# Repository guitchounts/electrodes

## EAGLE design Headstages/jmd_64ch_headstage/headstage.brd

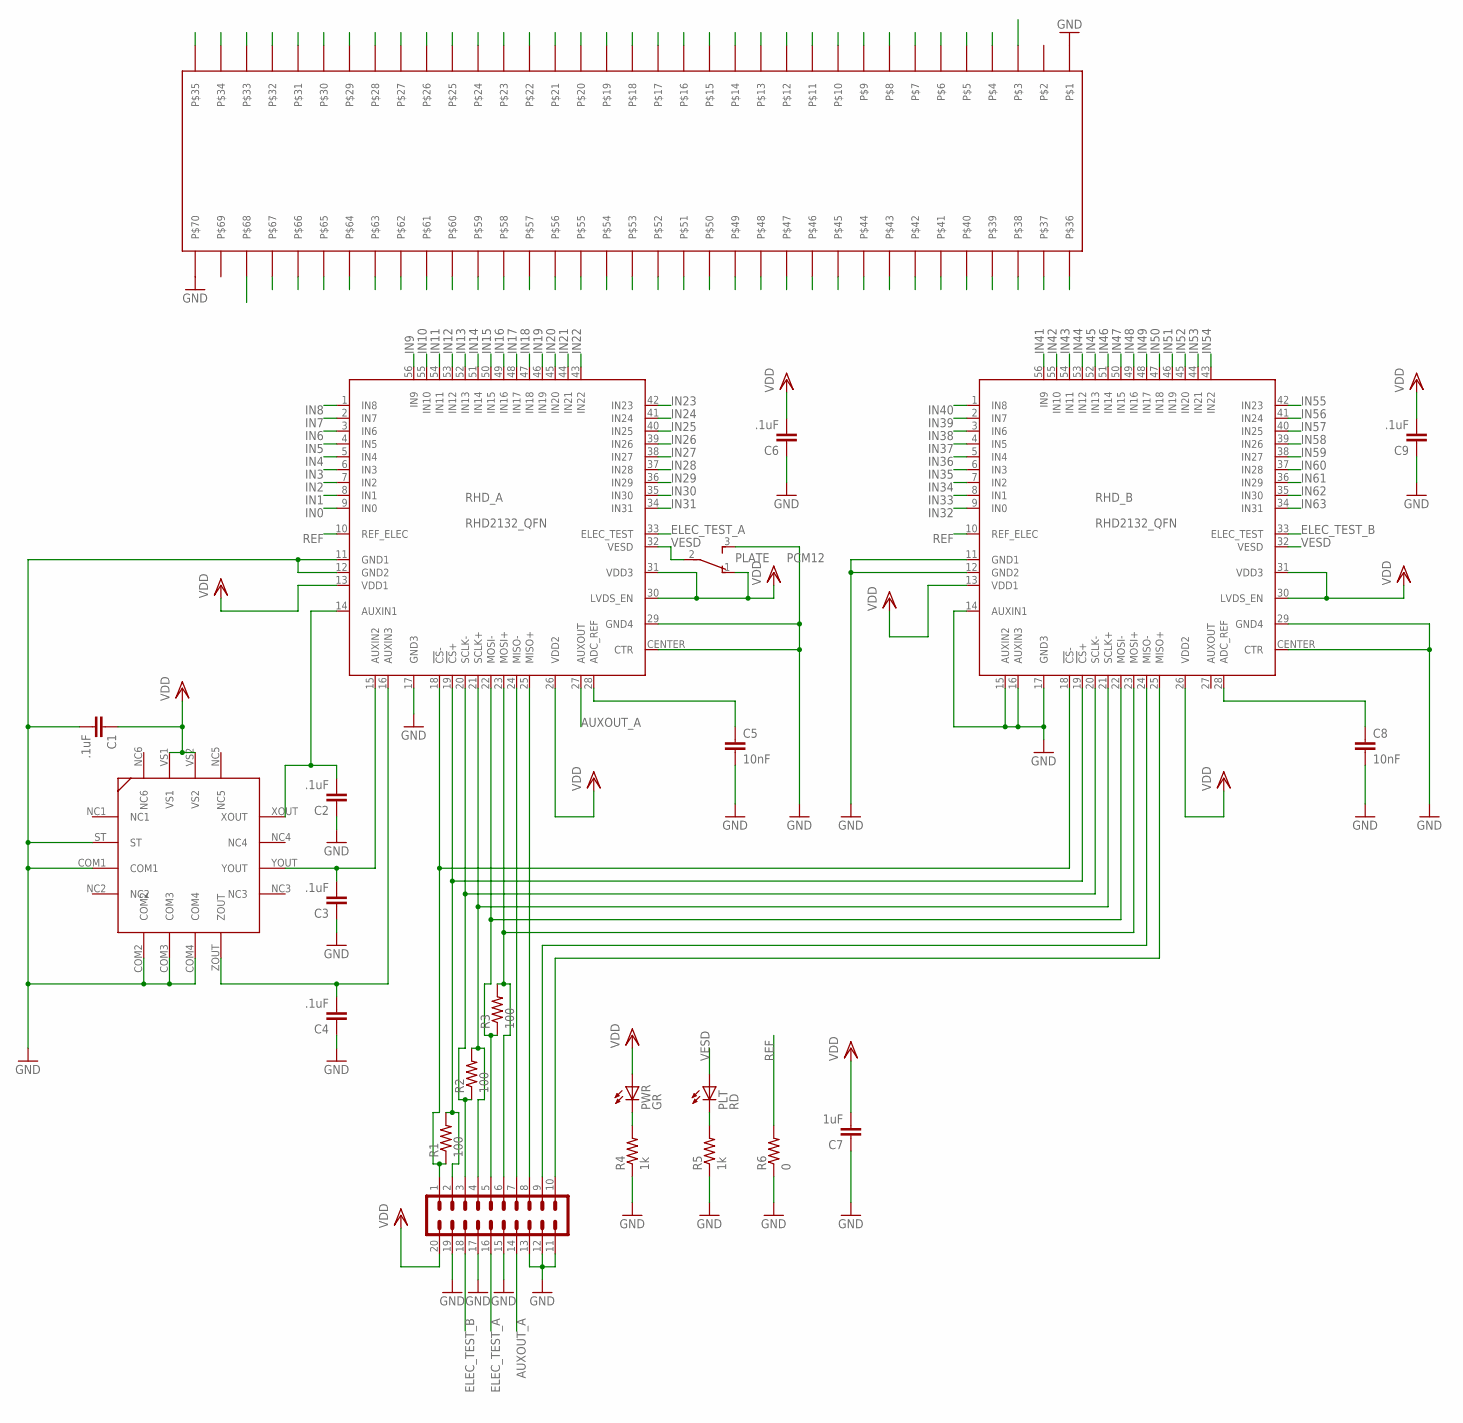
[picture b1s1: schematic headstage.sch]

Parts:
C1, C2, C3, C4: .1uF; 0402
C5, C8: 10nF; 0402
C6, C9: .1uF; 0603
C7: 1uF; 0603
OUT: JMD; JMD20-RA
PLATE: PCM12
PLT: RD; CHIP-LED0603
PWR: GR; CHIP-LED0603
R1, R2, R3: 100; 0402
R4, R5: 1k; 0402
R6: 0; 0402
RHD_A: RHD2132_QFN; QFN56_8_X_8_LARGE
RHD_B: RHD2132_QFN; QFN56_8_X_8_LARGE
U1: ADXL335
U$1: HIROSE_DF40_70PIN; HIROSE_DF40C-70DS

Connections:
AUXOUT_A: OUT.14, RHD_A.27 (AUXOUT)
CS+: OUT.2, R1.2, RHD_A.19 (!CS!+), RHD_B.19 (!CS!+)
CS-: OUT.1, R1.1, RHD_A.18 (!CS!-), RHD_B.18 (!CS!-)
ELEC_TEST_A: OUT.16, RHD_A.33 (ELEC_TEST)
ELEC_TEST_B: OUT.18, RHD_B.33 (ELEC_TEST)
GND: C1.2, C2.1, C3.1, C4.1, C5.2, C6.1, C7.1, C8.2, C9.1, OUT.11, OUT.12, OUT.13, OUT.15, OUT.17, OUT.19, PLATE.3, R4.1, R5.1, R6.1, RHD_A.11 (GND1), RHD_A.12 (GND2), RHD_A.17 (GND3), RHD_A.29 (GND4), RHD_A.CENTER (CTR), RHD_B.11 (GND1), RHD_B.12 (GND2), RHD_B.14 (AUXIN1), RHD_B.15 (AUXIN2), RHD_B.16 (AUXIN3), RHD_B.17 (GND3), RHD_B.29 (GND4), RHD_B.CENTER (CTR), U1.COM1, U1.COM2, U1.COM3, U1.COM4, U1.ST, U$1.P$1, U$1.P$70
IN0: RHD_A.9 (IN0), U$1.P$4
IN1: RHD_A.8 (IN1), U$1.P$5
IN2: RHD_A.7 (IN2), U$1.P$6
IN3: RHD_A.6 (IN3), U$1.P$7
IN4: RHD_A.5 (IN4), U$1.P$8
IN5: RHD_A.4 (IN5), U$1.P$9
IN6: RHD_A.3 (IN6), U$1.P$10
IN7: RHD_A.2 (IN7), U$1.P$11
IN8: RHD_A.1 (IN8), U$1.P$12
IN9: RHD_A.56 (IN9), U$1.P$13
IN10: RHD_A.55 (IN10), U$1.P$14
IN11: RHD_A.54 (IN11), U$1.P$15
IN12: RHD_A.53 (IN12), U$1.P$16
IN13: RHD_A.52 (IN13), U$1.P$17
IN14: RHD_A.51 (IN14), U$1.P$18
IN15: RHD_A.50 (IN15), U$1.P$19
IN16: RHD_A.49 (IN16), U$1.P$20
IN17: RHD_A.48 (IN17), U$1.P$21
IN18: RHD_A.47 (IN18), U$1.P$22
IN19: RHD_A.46 (IN19), U$1.P$23
IN20: RHD_A.45 (IN20), U$1.P$24
IN21: RHD_A.44 (IN21), U$1.P$25
IN22: RHD_A.43 (IN22), U$1.P$26
IN23: RHD_A.42 (IN23), U$1.P$27
IN24: RHD_A.41 (IN24), U$1.P$28
IN25: RHD_A.40 (IN25), U$1.P$29
IN26: RHD_A.39 (IN26), U$1.P$30
IN27: RHD_A.38 (IN27), U$1.P$31
IN28: RHD_A.37 (IN28), U$1.P$32
IN29: RHD_A.36 (IN29), U$1.P$33
IN30: RHD_A.35 (IN30), U$1.P$34
IN31: RHD_A.34 (IN31), U$1.P$35
IN32: RHD_B.9 (IN0), U$1.P$67
IN33: RHD_B.8 (IN1), U$1.P$66
IN34: RHD_B.7 (IN2), U$1.P$65
IN35: RHD_B.6 (IN3), U$1.P$64
IN36: RHD_B.5 (IN4), U$1.P$63
IN37: RHD_B.4 (IN5), U$1.P$62
IN38: RHD_B.3 (IN6), U$1.P$61
IN39: RHD_B.2 (IN7), U$1.P$60
IN40: RHD_B.1 (IN8), U$1.P$59
IN41: RHD_B.56 (IN9), U$1.P$58
IN42: RHD_B.55 (IN10), U$1.P$57
IN43: RHD_B.54 (IN11), U$1.P$56
IN44: RHD_B.53 (IN12), U$1.P$55
IN45: RHD_B.52 (IN13), U$1.P$54
IN46: RHD_B.51 (IN14), U$1.P$53
IN47: RHD_B.50 (IN15), U$1.P$52
IN48: RHD_B.49 (IN16), U$1.P$51
IN49: RHD_B.48 (IN17), U$1.P$50
IN50: RHD_B.47 (IN18), U$1.P$49
IN51: RHD_B.46 (IN19), U$1.P$48
IN52: RHD_B.45 (IN20), U$1.P$47
IN53: RHD_B.44 (IN21), U$1.P$46
IN54: RHD_B.43 (IN22), U$1.P$45
IN55: RHD_B.42 (IN23), U$1.P$44
IN56: RHD_B.41 (IN24), U$1.P$43
IN57: RHD_B.40 (IN25), U$1.P$42
IN58: RHD_B.39 (IN26), U$1.P$41
IN59: RHD_B.38 (IN27), U$1.P$40
IN60: RHD_B.37 (IN28), U$1.P$39
IN61: RHD_B.36 (IN29), U$1.P$38
IN62: RHD_B.35 (IN30), U$1.P$37
IN63: RHD_B.34 (IN31), U$1.P$36
LEDOUT1: PWR.C, R4.2
LEDOUT2: PLT.C, R5.2
MIS02-: OUT.9, RHD_B.24 (MISO-)
MISO1+: OUT.8, RHD_A.25 (MISO+)
MISO1-: OUT.7, RHD_A.24 (MISO-)
MISO2+: OUT.10, RHD_B.25 (MISO+)
MOSI+: OUT.6, R3.2, RHD_A.23 (MOSI+), RHD_B.23 (MOSI+)
MOSI-: OUT.5, R3.1, RHD_A.22 (MOSI-), RHD_B.22 (MOSI-)
unnamed: C8.1, RHD_B.28 (ADC_REF)
unnamed: C5.1, RHD_A.28 (ADC_REF)
REF: R6.2, RHD_A.10 (REF_ELEC), RHD_B.10 (REF_ELEC), U$1.P$3, U$1.P$68
SCLK+: OUT.4, R2.2, RHD_A.21 (SCLK+), RHD_B.21 (SCLK+)
SCLK-: OUT.3, R2.1, RHD_A.20 (SCLK-), RHD_B.20 (SCLK-)
VDD: C1.1, C6.2, C7.2, C9.2, OUT.20, PLATE.1, PWR.A, RHD_A.13 (VDD1), RHD_A.26 (VDD2), RHD_A.30 (LVDS_EN), RHD_A.31 (VDD3), RHD_B.13 (VDD1), RHD_B.26 (VDD2), RHD_B.30 (LVDS_EN), RHD_B.31 (VDD3), U1.VS1, U1.VS2
VESD: PLATE.2, PLT.A, RHD_A.32 (VESD), RHD_B.32 (VESD)
XOUT1: C2.2, RHD_A.14 (AUXIN1), U1.XOUT
YOUT1: C3.2, RHD_A.15 (AUXIN2), U1.YOUT
ZOUT1: C4.2, RHD_A.16 (AUXIN3), U1.ZOUT

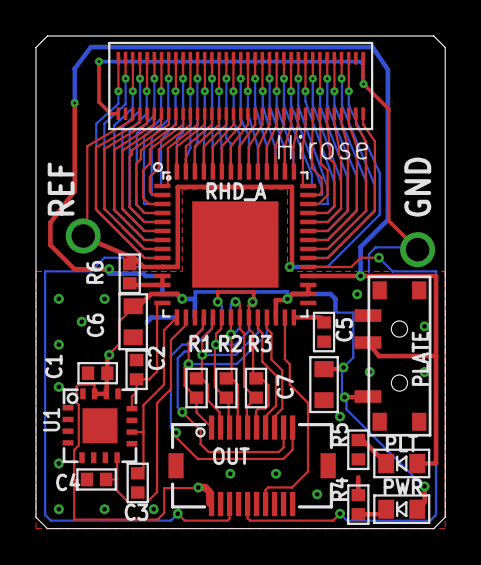
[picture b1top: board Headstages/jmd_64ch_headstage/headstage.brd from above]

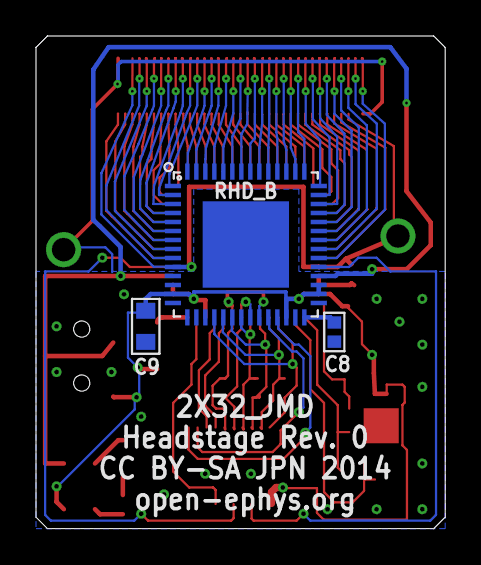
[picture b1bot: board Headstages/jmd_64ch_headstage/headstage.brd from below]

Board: 4 copper layers, 22.7 x 27.4 mm, 23 parts (3 on the bottom side), 88 nets.

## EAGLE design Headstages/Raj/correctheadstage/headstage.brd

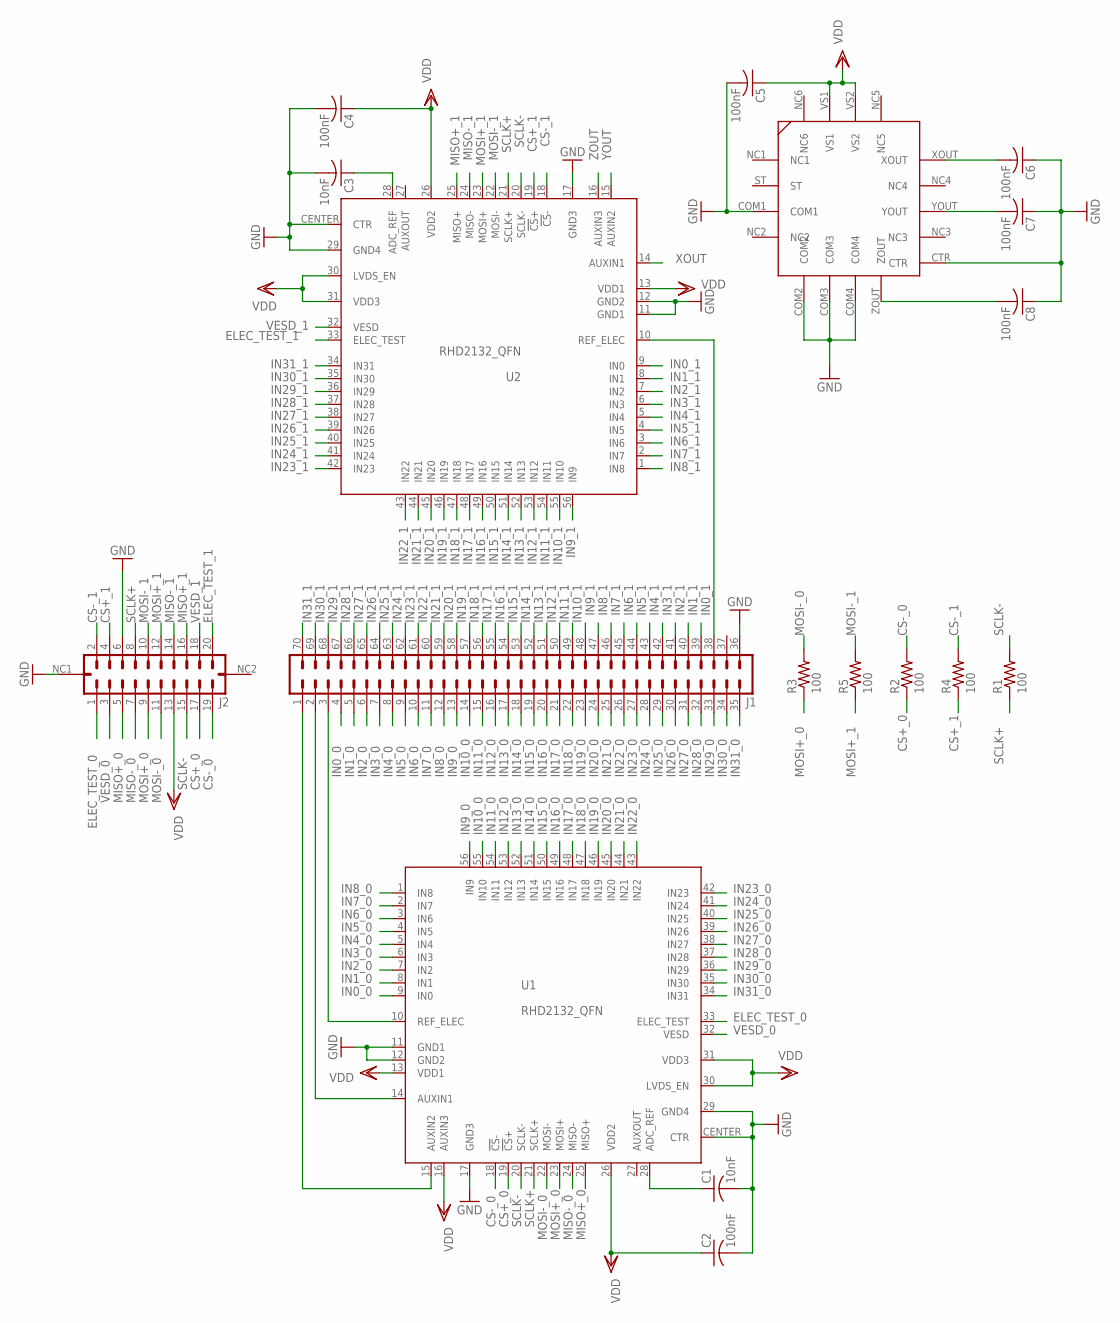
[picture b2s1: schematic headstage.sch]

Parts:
C1, C3: 10nF; C0402K
C2, C4, C5, C6, C7, C8: 100nF; C0402K
J1: HIROSE_DF40C-70DS-0.4V(51); HIROSE_DF40C-70DP
J2: MOLEX_501190-2017
R1, R2, R3, R4, R5: 100; R0402
U1, U2: RHD2132_QFN; QFN56_8_X_8_LARGE
U3: ADXL335

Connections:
CS+_0: J2.17, R2.1, U1.19 (!CS!+)
CS+_1: J2.4, R4.1, U2.19 (!CS!+)
CS-_0: J2.19, R2.2, U1.18 (!CS!-)
CS-_1: J2.2, R4.2, U2.18 (!CS!-)
ELEC_TEST_0: J2.1, U1.33 (ELEC_TEST)
ELEC_TEST_1: J2.20, U2.33 (ELEC_TEST)
GND: C1.2, C2.2, C3.2, C4.2, C5.2, C6.1, C7.1, C8.1, J1.36, J2.6, J2.NC1, U1.11 (GND1), U1.12 (GND2), U1.17 (GND3), U1.29 (GND4), U1.CENTER (CTR), U2.11 (GND1), U2.12 (GND2), U2.17 (GND3), U2.29 (GND4), U2.CENTER (CTR), U3.COM1, U3.COM2, U3.COM3, U3.COM4, U3.CTR
IN0_0: J1.4, U1.9 (IN0)
IN0_1: J1.39, U2.9 (IN0)
IN1_0: J1.5, U1.8 (IN1)
IN1_1: J1.40, U2.8 (IN1)
IN2_0: J1.6, U1.7 (IN2)
IN2_1: J1.41, U2.7 (IN2)
IN3_0: J1.7, U1.6 (IN3)
IN3_1: J1.42, U2.6 (IN3)
IN4_0: J1.8, U1.5 (IN4)
IN4_1: J1.43, U2.5 (IN4)
IN5_0: J1.9, U1.4 (IN5)
IN5_1: J1.44, U2.4 (IN5)
IN6_0: J1.10, U1.3 (IN6)
IN6_1: J1.45, U2.3 (IN6)
IN7_0: J1.11, U1.2 (IN7)
IN7_1: J1.46, U2.2 (IN7)
IN8_0: J1.12, U1.1 (IN8)
IN8_1: J1.47, U2.1 (IN8)
IN9_0: J1.13, U1.56 (IN9)
IN9_1: J1.48, U2.56 (IN9)
IN10_0: J1.14, U1.55 (IN10)
IN10_1: J1.49, U2.55 (IN10)
IN11_0: J1.15, U1.54 (IN11)
IN11_1: J1.50, U2.54 (IN11)
IN12_0: J1.16, U1.53 (IN12)
IN12_1: J1.51, U2.53 (IN12)
IN13_0: J1.17, U1.52 (IN13)
IN13_1: J1.52, U2.52 (IN13)
IN14_0: J1.18, U1.51 (IN14)
IN14_1: J1.53, U2.51 (IN14)
IN15_0: J1.19, U1.50 (IN15)
IN15_1: J1.54, U2.50 (IN15)
IN16_0: J1.20, U1.49 (IN16)
IN16_1: J1.55, U2.49 (IN16)
IN17_0: J1.21, U1.48 (IN17)
IN17_1: J1.56, U2.48 (IN17)
IN18_0: J1.22, U1.47 (IN18)
IN18_1: J1.57, U2.47 (IN18)
IN19_0: J1.23, U1.46 (IN19)
IN19_1: J1.58, U2.46 (IN19)
IN20_0: J1.24, U1.45 (IN20)
IN20_1: J1.59, U2.45 (IN20)
IN21_0: J1.25, U1.44 (IN21)
IN21_1: J1.60, U2.44 (IN21)
IN22_0: J1.26, U1.43 (IN22)
IN22_1: J1.61, U2.43 (IN22)
IN23_0: J1.27, U1.42 (IN23)
IN23_1: J1.62, U2.42 (IN23)
IN24_0: J1.28, U1.41 (IN24)
IN24_1: J1.63, U2.41 (IN24)
IN25_0: J1.29, U1.40 (IN25)
IN25_1: J1.64, U2.40 (IN25)
IN26_0: J1.30, U1.39 (IN26)
IN26_1: J1.65, U2.39 (IN26)
IN27_0: J1.31, U1.38 (IN27)
IN27_1: J1.66, U2.38 (IN27)
IN28_0: J1.32, U1.37 (IN28)
IN28_1: J1.67, U2.37 (IN28)
IN29_0: J1.33, U1.36 (IN29)
IN29_1: J1.68, U2.36 (IN29)
IN30_0: J1.34, U1.35 (IN30)
IN30_1: J1.69, U2.35 (IN30)
IN31_0: J1.35, U1.34 (IN31)
IN31_1: J1.70, U2.34 (IN31)
MISO+_0: J2.5, U1.25 (MISO+)
MISO+_1: J2.16, U2.25 (MISO+)
MISO-_0: J2.7, U1.24 (MISO-)
MISO-_1: J2.14, U2.24 (MISO-)
MOSI+_0: J2.9, R3.1, U1.23 (MOSI+)
MOSI+_1: J2.12, R5.1, U2.23 (MOSI+)
MOSI-_0: J2.11, R3.2, U1.22 (MOSI-)
MOSI-_1: J2.10, R5.2, U2.22 (MOSI-)
unnamed: J1.1, U1.15 (AUXIN2)
unnamed: J1.2, U1.14 (AUXIN1)
unnamed: C1.1, U1.28 (ADC_REF)
unnamed: C3.1, U2.28 (ADC_REF)
REF_ELEC_0: J1.3, U1.10 (REF_ELEC)
REF_ELEC_1: J1.38, U2.10 (REF_ELEC)
SCLK+: J2.8, R1.1, U1.21 (SCLK+), U2.21 (SCLK+)
SCLK-: J2.15, R1.2, U1.20 (SCLK-), U2.20 (SCLK-)
VDD: C2.1, C4.1, C5.1, J2.13, U1.13 (VDD1), U1.16 (AUXIN3), U1.26 (VDD2), U1.30 (LVDS_EN), U1.31 (VDD3), U2.13 (VDD1), U2.26 (VDD2), U2.30 (LVDS_EN), U2.31 (VDD3), U3.VS1, U3.VS2
VESD_0: J2.3, U1.32 (VESD)
VESD_1: J2.18, U2.32 (VESD)
XOUT: C6.2, U2.14 (AUXIN1), U3.XOUT
YOUT: C7.2, U2.15 (AUXIN2), U3.YOUT
ZOUT: C8.2, U2.16 (AUXIN3), U3.ZOUT

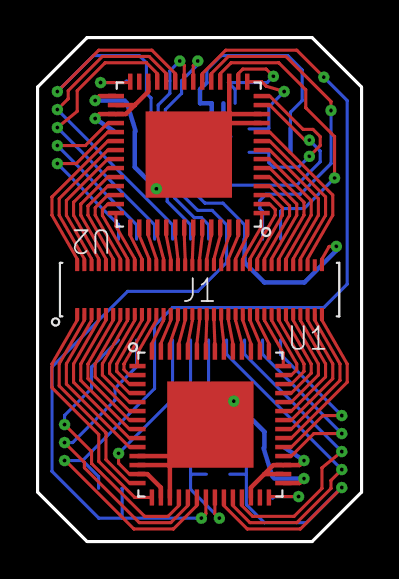
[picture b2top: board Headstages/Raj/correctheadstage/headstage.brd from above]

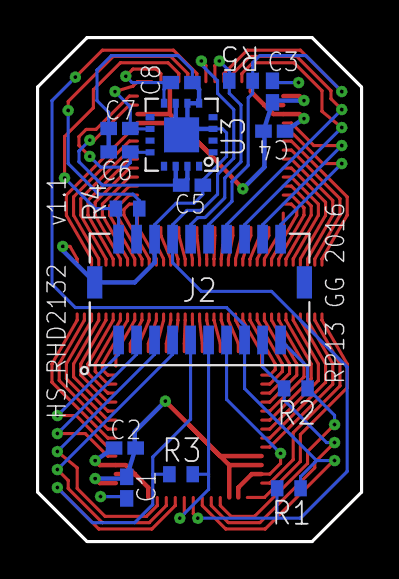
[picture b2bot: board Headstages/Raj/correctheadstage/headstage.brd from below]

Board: 4 copper layers, 18.0 x 28.0 mm, 18 parts (15 on the bottom side), 93 nets.

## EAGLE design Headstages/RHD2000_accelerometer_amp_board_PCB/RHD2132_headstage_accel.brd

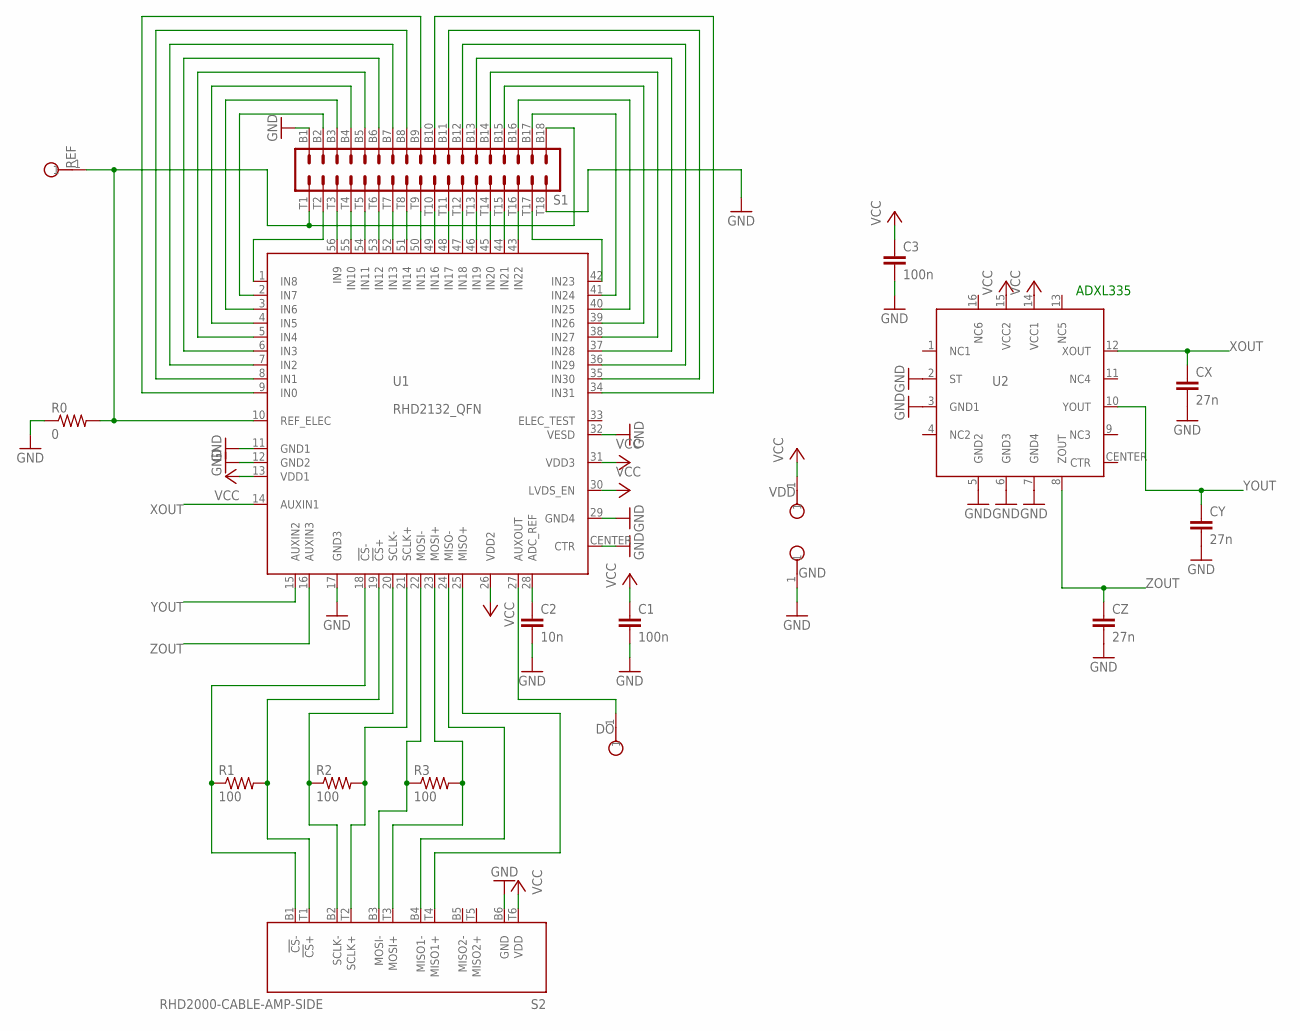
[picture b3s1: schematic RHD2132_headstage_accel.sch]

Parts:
C1, C3: 100n; 0402
C2: 10n; 0402
CX: 27n; 0402
CY: 27n; 0402
CZ: 27n; 0402
DO: TESTPOINT_SMALL
GND: TESTPOINT_SMALL
R0: 0; 0402
R1, R2, R3: 100; 0402
REF: TESTPOINT_SMALL
S1: OMNETICS_A79025
S2: RHD2000-CABLE-AMP-SIDE; OMNETICS_PZN-12-AA
U1: RHD2132_QFN; QFN56_8_X_8_LARGE
U2: ADXL335
VDD: TESTPOINT_SMALL

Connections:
GND: C1.2, C2.2, C3.2, CX.2, CY.2, CZ.2, GND.1, R0.1, S1.B1, S1.T18, S2.B6 (GND), U1.11 (GND1), U1.12 (GND2), U1.17 (GND3), U1.29 (GND4), U1.32 (VESD), U1.CENTER (CTR), U2.2 (ST), U2.3 (GND1), U2.5 (GND2), U2.6 (GND3), U2.7 (GND4)
unnamed: R0.2, REF.1, S1.B18, S1.T1, U1.10 (REF_ELEC)
unnamed: S1.B3, U1.3 (IN6)
unnamed: S1.B2, U1.2 (IN7)
unnamed: S1.B4, U1.4 (IN5)
unnamed: S1.B5, U1.5 (IN4)
unnamed: S1.B6, U1.6 (IN3)
unnamed: S1.B7, U1.7 (IN2)
unnamed: S1.B8, U1.8 (IN1)
unnamed: S1.B9, U1.9 (IN0)
unnamed: S1.B10, U1.34 (IN31)
unnamed: R1.1, S2.B1 (!CS!-), U1.18 (!CS!-)
unnamed: S1.B17, U1.41 (IN24)
unnamed: S1.B16, U1.40 (IN25)
unnamed: S1.B15, U1.39 (IN26)
unnamed: S1.B14, U1.38 (IN27)
unnamed: S1.B13, U1.37 (IN28)
unnamed: S1.B12, U1.36 (IN29)
unnamed: S1.B11, U1.35 (IN30)
unnamed: S1.T9, U1.50 (IN15)
unnamed: S1.T8, U1.51 (IN14)
unnamed: S1.T7, U1.52 (IN13)
unnamed: S1.T3, U1.56 (IN9)
unnamed: S1.T4, U1.55 (IN10)
unnamed: S1.T5, U1.54 (IN11)
unnamed: S1.T6, U1.53 (IN12)
unnamed: S1.T10, U1.49 (IN16)
unnamed: S1.T11, U1.48 (IN17)
unnamed: S1.T12, U1.47 (IN18)
unnamed: S1.T13, U1.46 (IN19)
unnamed: S1.T14, U1.45 (IN20)
unnamed: S1.T15, U1.44 (IN21)
unnamed: S1.T16, U1.43 (IN22)
unnamed: S1.T2, U1.1 (IN8)
unnamed: S1.T17, U1.42 (IN23)
unnamed: R1.2, S2.T1 (!CS!+), U1.19 (!CS!+)
unnamed: R2.1, S2.B2 (SCLK-), U1.20 (SCLK-)
unnamed: R2.2, S2.T2 (SCLK+), U1.21 (SCLK+)
unnamed: R3.1, S2.B3 (MOSI-), U1.22 (MOSI-)
unnamed: R3.2, S2.T3 (MOSI+), U1.23 (MOSI+)
unnamed: S2.B4 (MISO1-), U1.24 (MISO-)
unnamed: S2.T4 (MISO1+), U1.25 (MISO+)
unnamed: C2.1, U1.28 (ADC_REF)
unnamed: DO.1, U1.27 (AUXOUT)
VCC: C1.1, C3.1, S2.T6 (VDD), U1.13 (VDD1), U1.26 (VDD2), U1.30 (LVDS_EN), U1.31 (VDD3), U2.14 (VCC1), U2.15 (VCC2), VDD.1
XOUT: CX.1, U1.14 (AUXIN1), U2.12 (XOUT)
YOUT: CY.1, U1.15 (AUXIN2), U2.10 (YOUT)
ZOUT: CZ.1, U1.16 (AUXIN3), U2.8 (ZOUT)

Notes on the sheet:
ADXL335

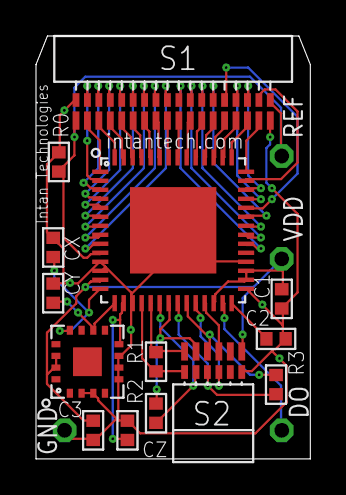
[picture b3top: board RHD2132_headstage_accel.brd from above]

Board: 4 copper layers, 15.2 x 23.5 mm, 18 parts (0 on the bottom side), 48 nets.

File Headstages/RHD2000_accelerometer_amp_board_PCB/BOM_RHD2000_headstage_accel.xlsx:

Bill of Materials |  | RHD2000 Headstage Accel Board |  | Intan Technologies, LLC
Part | Value | Device | Package | Digi-Key part number | Notes
C1 | 100 nF (0.1 uF) | ceramic capacitor (25 V) | 0402 | 445-4964-1-ND
C2 | 10 nF (10000 pF) | ceramic capacitor (25 V) | 0402 | 490-1312-1-ND
C3 | 100 nF (0.1 uF) | ceramic capacitor (25 V) | 0402 | 445-4964-1-ND
CX | 27 nF | ceramic capacitor (16 V) | 0402 | 399-4888-1-ND
CY | 27 nF | ceramic capacitor (16 V) | 0402 | 399-4888-1-ND
CZ | 27 nF | ceramic capacitor (16 V) | 0402 | 399-4888-1-ND
R0 | 0 | resistor | 0402 | P0.0JCT-ND
R1 | 100 | resistor | 0402 | P100JCT-ND
R2 | 100 | resistor | 0402 | P100JCT-ND
R3 | 100 | resistor | 0402 | P100JCT-ND
S1 | NSD-36-AA-GS | nano strip connector | 36-pin, 4 guides | Omnetics A79025-001
S2 | PZN-12-AA | polarized nano connector | polarized 12-pin | Omnetics A79623-001
U1 | RHD2132 or RHD2216 | 32-channel amplifier chip | QFN-56L | Intan RHD2132/RHD2216
U2 | ADXL335 | 3-axis accelerometer | LQFN-16 | ADXL335BCPZ-RL7CT-ND

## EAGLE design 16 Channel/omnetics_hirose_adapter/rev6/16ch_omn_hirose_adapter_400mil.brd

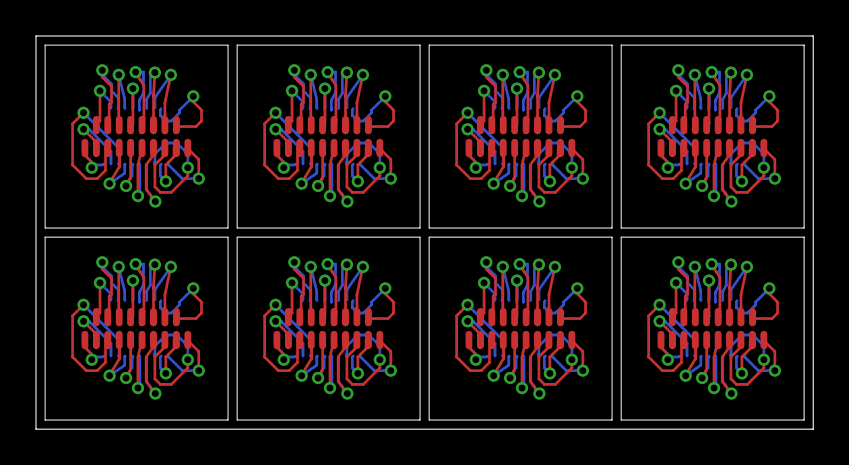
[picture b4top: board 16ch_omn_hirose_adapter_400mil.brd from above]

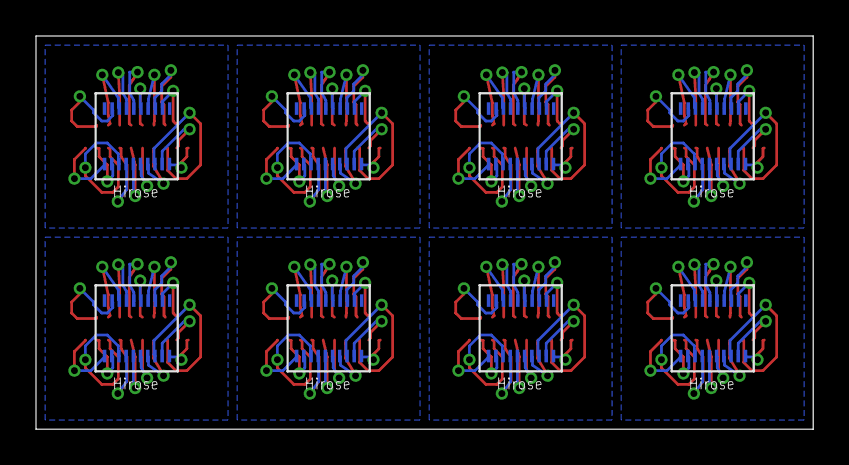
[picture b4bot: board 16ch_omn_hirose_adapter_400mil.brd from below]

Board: 2 copper layers, 43.2 x 21.8 mm, 16 parts (8 on the bottom side), 144 nets.

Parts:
U$1, U$3, U$5, U$7, U$9, U$11, U$13, U$15: HIROSE_DF40_70PIN; HIROSE_DF40C-70DS
U$2, U$4, U$6, U$8, U$10, U$12, U$14, U$16: OMNETICS_FE18

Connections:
unnamed: U$1.P$10, U$2.P$18
unnamed: U$1.P$9, U$2.P$8
unnamed: U$1.P$8, U$2.P$7
unnamed: U$1.P$7, U$2.P$6
unnamed: U$1.P$6, U$2.P$5
unnamed: U$1.P$5, U$2.P$4
unnamed: U$1.P$4, U$2.P$3
unnamed: U$1.P$3, U$2.P$2
unnamed: U$1.P$2, U$2.P$1
unnamed: U$1.P$1, U$2.P$17
unnamed: U$1.P$44, U$2.P$9
unnamed: U$1.P$43, U$2.P$10
unnamed: U$1.P$42, U$2.P$11
unnamed: U$1.P$41, U$2.P$12
unnamed: U$1.P$40, U$2.P$13
unnamed: U$1.P$39, U$2.P$14
unnamed: U$1.P$38, U$2.P$15
unnamed: U$1.P$37, U$2.P$16
unnamed: U$3.P$10, U$4.P$18
unnamed: U$3.P$9, U$4.P$8
unnamed: U$3.P$8, U$4.P$7
unnamed: U$3.P$7, U$4.P$6
unnamed: U$3.P$6, U$4.P$5
unnamed: U$3.P$5, U$4.P$4
unnamed: U$3.P$4, U$4.P$3
unnamed: U$3.P$3, U$4.P$2
unnamed: U$3.P$2, U$4.P$1
unnamed: U$3.P$1, U$4.P$17
unnamed: U$3.P$44, U$4.P$9
unnamed: U$3.P$43, U$4.P$10
unnamed: U$3.P$42, U$4.P$11
unnamed: U$3.P$41, U$4.P$12
unnamed: U$3.P$40, U$4.P$13
unnamed: U$3.P$39, U$4.P$14
unnamed: U$3.P$38, U$4.P$15
unnamed: U$3.P$37, U$4.P$16
unnamed: U$5.P$10, U$6.P$18
unnamed: U$5.P$9, U$6.P$8
unnamed: U$5.P$8, U$6.P$7
unnamed: U$5.P$7, U$6.P$6
unnamed: U$5.P$6, U$6.P$5
unnamed: U$5.P$5, U$6.P$4
unnamed: U$5.P$4, U$6.P$3
unnamed: U$5.P$3, U$6.P$2
unnamed: U$5.P$2, U$6.P$1
unnamed: U$5.P$1, U$6.P$17
unnamed: U$5.P$44, U$6.P$9
unnamed: U$5.P$43, U$6.P$10
unnamed: U$5.P$42, U$6.P$11
unnamed: U$5.P$41, U$6.P$12
unnamed: U$5.P$40, U$6.P$13
unnamed: U$5.P$39, U$6.P$14
unnamed: U$5.P$38, U$6.P$15
unnamed: U$5.P$37, U$6.P$16
unnamed: U$7.P$10, U$8.P$18
unnamed: U$7.P$9, U$8.P$8
unnamed: U$7.P$8, U$8.P$7
unnamed: U$7.P$7, U$8.P$6
unnamed: U$7.P$6, U$8.P$5
unnamed: U$7.P$5, U$8.P$4
unnamed: U$7.P$4, U$8.P$3
unnamed: U$7.P$3, U$8.P$2
unnamed: U$7.P$2, U$8.P$1
unnamed: U$7.P$1, U$8.P$17
unnamed: U$7.P$44, U$8.P$9
unnamed: U$7.P$43, U$8.P$10
unnamed: U$7.P$42, U$8.P$11
unnamed: U$7.P$41, U$8.P$12
unnamed: U$7.P$40, U$8.P$13
unnamed: U$7.P$39, U$8.P$14
unnamed: U$7.P$38, U$8.P$15
unnamed: U$7.P$37, U$8.P$16
unnamed: U$9.P$10, U$10.P$18
unnamed: U$9.P$9, U$10.P$8
unnamed: U$9.P$8, U$10.P$7
unnamed: U$9.P$7, U$10.P$6
unnamed: U$9.P$6, U$10.P$5
unnamed: U$9.P$5, U$10.P$4
unnamed: U$9.P$4, U$10.P$3
unnamed: U$9.P$3, U$10.P$2
unnamed: U$9.P$2, U$10.P$1
unnamed: U$9.P$1, U$10.P$17
unnamed: U$9.P$44, U$10.P$9
unnamed: U$9.P$43, U$10.P$10
unnamed: U$9.P$42, U$10.P$11
unnamed: U$9.P$41, U$10.P$12
unnamed: U$9.P$40, U$10.P$13
unnamed: U$9.P$39, U$10.P$14
unnamed: U$9.P$38, U$10.P$15
unnamed: U$9.P$37, U$10.P$16
unnamed: U$11.P$10, U$12.P$18
unnamed: U$11.P$9, U$12.P$8
unnamed: U$11.P$8, U$12.P$7
unnamed: U$11.P$7, U$12.P$6
unnamed: U$11.P$6, U$12.P$5
unnamed: U$11.P$5, U$12.P$4
unnamed: U$11.P$4, U$12.P$3
unnamed: U$11.P$3, U$12.P$2
unnamed: U$11.P$2, U$12.P$1
unnamed: U$11.P$1, U$12.P$17
unnamed: U$11.P$44, U$12.P$9
unnamed: U$11.P$43, U$12.P$10
unnamed: U$11.P$42, U$12.P$11
unnamed: U$11.P$41, U$12.P$12
unnamed: U$11.P$40, U$12.P$13
unnamed: U$11.P$39, U$12.P$14
unnamed: U$11.P$38, U$12.P$15
unnamed: U$11.P$37, U$12.P$16
unnamed: U$13.P$10, U$14.P$18
unnamed: U$13.P$9, U$14.P$8
unnamed: U$13.P$8, U$14.P$7
unnamed: U$13.P$7, U$14.P$6
unnamed: U$13.P$6, U$14.P$5
unnamed: U$13.P$5, U$14.P$4
unnamed: U$13.P$4, U$14.P$3
unnamed: U$13.P$3, U$14.P$2
unnamed: U$13.P$2, U$14.P$1
unnamed: U$13.P$1, U$14.P$17
unnamed: U$13.P$44, U$14.P$9
unnamed: U$13.P$43, U$14.P$10
unnamed: U$13.P$42, U$14.P$11
unnamed: U$13.P$41, U$14.P$12
unnamed: U$13.P$40, U$14.P$13
unnamed: U$13.P$39, U$14.P$14
unnamed: U$13.P$38, U$14.P$15
unnamed: U$13.P$37, U$14.P$16
unnamed: U$15.P$10, U$16.P$18
unnamed: U$15.P$9, U$16.P$8
unnamed: U$15.P$8, U$16.P$7
unnamed: U$15.P$7, U$16.P$6
unnamed: U$15.P$6, U$16.P$5
unnamed: U$15.P$5, U$16.P$4
unnamed: U$15.P$4, U$16.P$3
unnamed: U$15.P$3, U$16.P$2
unnamed: U$15.P$2, U$16.P$1
unnamed: U$15.P$1, U$16.P$17
unnamed: U$15.P$44, U$16.P$9
unnamed: U$15.P$43, U$16.P$10
unnamed: U$15.P$42, U$16.P$11
unnamed: U$15.P$41, U$16.P$12
unnamed: U$15.P$40, U$16.P$13
unnamed: U$15.P$39, U$16.P$14
unnamed: U$15.P$38, U$16.P$15
unnamed: U$15.P$37, U$16.P$16

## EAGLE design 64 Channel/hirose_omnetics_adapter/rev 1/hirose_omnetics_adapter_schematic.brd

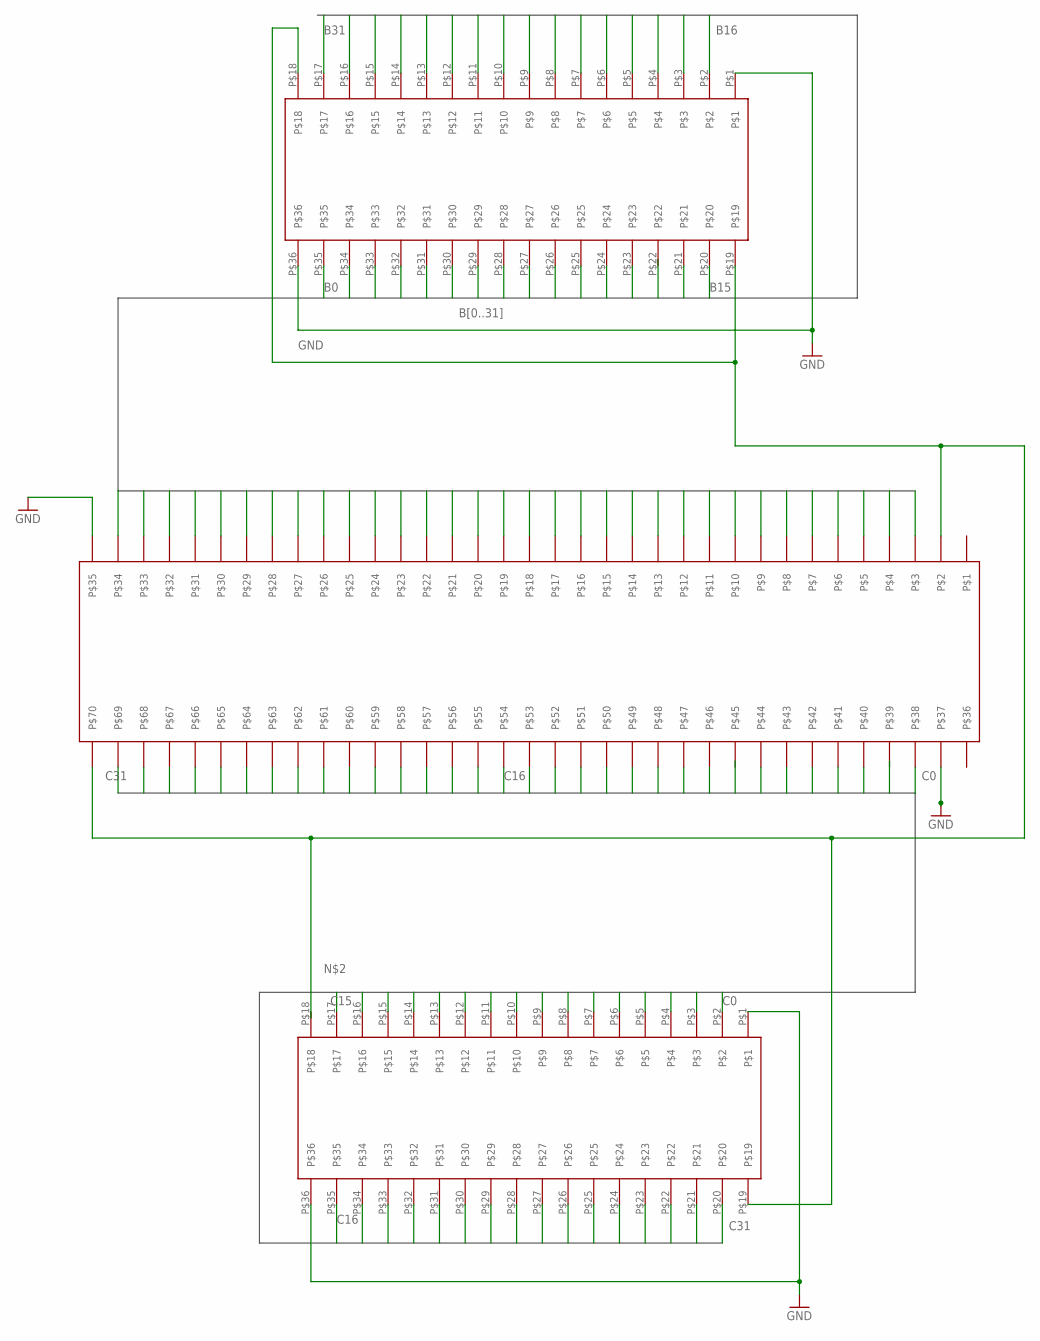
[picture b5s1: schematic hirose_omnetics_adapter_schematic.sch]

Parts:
U$1: HIROSE_DF40_70PIN; HIROSE_DF40C-70DS
U$2, U$3: OMNETICS_A79026; OMNETICS_A79026-001

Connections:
B0: U$1.P$3, U$2.P$35
B1: U$1.P$4, U$2.P$34
B2: U$1.P$5, U$2.P$33
B3: U$1.P$6, U$2.P$32
B4: U$1.P$7, U$2.P$31
B5: U$1.P$8, U$2.P$30
B6: U$1.P$9, U$2.P$29
B7: U$1.P$10, U$2.P$28
B8: U$1.P$11, U$2.P$27
B9: U$1.P$12, U$2.P$26
B10: U$1.P$13, U$2.P$25
B11: U$1.P$14, U$2.P$24
B12: U$1.P$15, U$2.P$23
B13: U$1.P$16
B14: U$1.P$17, U$2.P$21
B15: U$1.P$18, U$2.P$20
B16: U$1.P$19, U$2.P$2
B17: U$1.P$20, U$2.P$3
B18: U$1.P$21, U$2.P$4
B19: U$1.P$22, U$2.P$5
B20: U$1.P$23, U$2.P$6
B21: U$1.P$24, U$2.P$7
B22: U$1.P$25, U$2.P$8
B23: U$1.P$26, U$2.P$9
B24: U$1.P$27, U$2.P$10
B25: U$1.P$28, U$2.P$11
B26: U$1.P$29, U$2.P$12
B27: U$1.P$30, U$2.P$13
B28: U$1.P$31, U$2.P$14
B29: U$1.P$32, U$2.P$15
B30: U$1.P$33, U$2.P$16
B31: U$1.P$34, U$2.P$17
C0: U$1.P$38, U$3.P$2
C1: U$3.P$3
C2: U$1.P$40, U$3.P$4
C3: U$1.P$41, U$3.P$5
C4: U$1.P$42, U$3.P$6
C5: U$1.P$43, U$3.P$7
C6: U$1.P$44, U$3.P$8
C7: U$3.P$9
C8: U$1.P$46, U$3.P$10
C9: U$1.P$47, U$3.P$11
C10: U$1.P$48, U$3.P$12
C11: U$1.P$49, U$3.P$13
C12: U$1.P$50, U$3.P$14
C13: U$1.P$51, U$3.P$15
C14: U$1.P$52, U$3.P$16
C15: U$1.P$53, U$3.P$17
C16: U$1.P$54, U$3.P$35
C17: U$1.P$55, U$3.P$34
C18: U$1.P$56, U$3.P$33
C19: U$1.P$57, U$3.P$32
C20: U$1.P$58, U$3.P$31
C21: U$1.P$59, U$3.P$30
C22: U$1.P$60, U$3.P$29
C23: U$1.P$61, U$3.P$28
C24: U$1.P$62, U$3.P$27
C25: U$1.P$63, U$3.P$26
C26: U$1.P$64, U$3.P$25
C27: U$1.P$65, U$3.P$24
C28: U$1.P$66, U$3.P$23
C29: U$1.P$67, U$3.P$22
C30: U$1.P$68, U$3.P$21
C31: U$1.P$69, U$3.P$20
GND: U$1.P$35, U$1.P$37, U$2.P$1, U$2.P$36, U$3.P$1, U$3.P$36
unnamed: U$1.P$2, U$1.P$70, U$2.P$18, U$2.P$19, U$3.P$19

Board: 2 copper layers, 3 parts (1 on the bottom side), 63 nets, no tracks yet.

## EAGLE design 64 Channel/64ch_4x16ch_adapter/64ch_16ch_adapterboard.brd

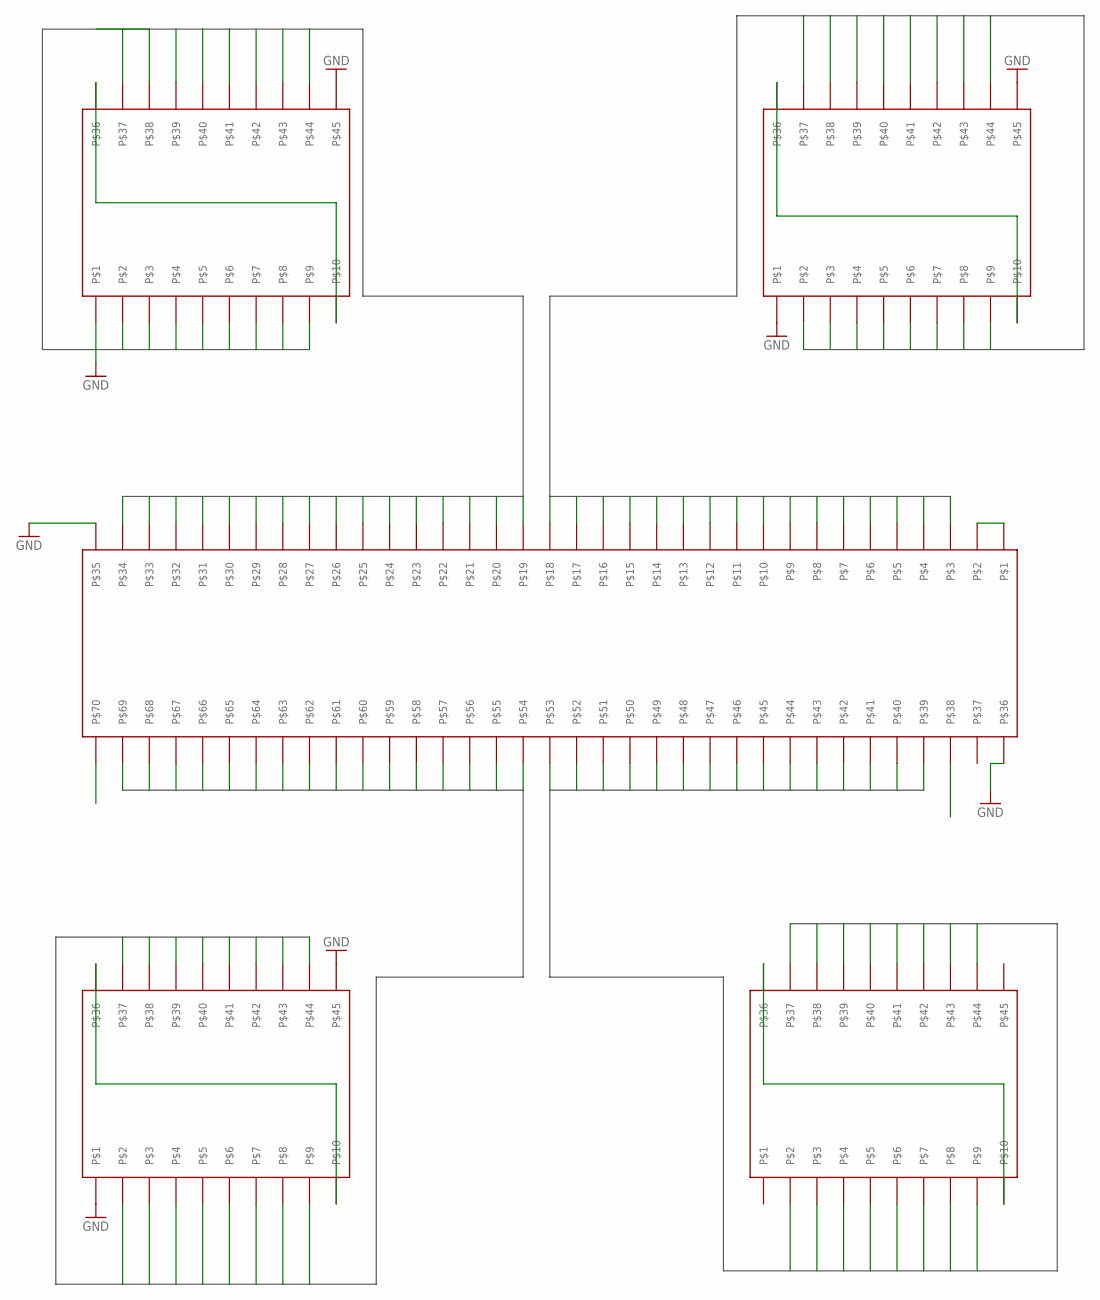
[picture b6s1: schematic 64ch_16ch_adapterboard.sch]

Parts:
U$1, U$2, U$3, U$4, U$5: HIROSE_DF40_70PIN; HIROSE_DF40C-70DS

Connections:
A0: U$1.P$34, U$3.P$44
A1: U$1.P$33, U$3.P$9
A2: U$1.P$32, U$3.P$8
A3: U$1.P$31, U$3.P$7
A4: U$1.P$30, U$3.P$6
A5: U$1.P$29, U$3.P$5
A6: U$1.P$28, U$3.P$4
A7: U$1.P$27, U$3.P$3
A8: U$1.P$26, U$3.P$2
A9: U$1.P$25, U$3.P$37
A10: U$1.P$22, U$3.P$38
A11: U$1.P$21, U$3.P$39
A12: U$1.P$23, U$3.P$40
A13: U$1.P$20, U$3.P$41
A14: U$1.P$24, U$3.P$42
A15: U$1.P$19, U$3.P$43
B0: U$1.P$3, U$2.P$37
B1: U$1.P$4, U$2.P$2
B2: U$1.P$5, U$2.P$3
B3: U$1.P$6, U$2.P$4
B4: U$1.P$7, U$2.P$5
B5: U$1.P$8, U$2.P$6
B6: U$1.P$9, U$2.P$7
B7: U$1.P$10, U$2.P$8
B8: U$1.P$11, U$2.P$9
B9: U$1.P$12, U$2.P$44
B10: U$1.P$15, U$2.P$43
B11: U$1.P$16, U$2.P$42
B12: U$1.P$14, U$2.P$41
B13: U$1.P$17, U$2.P$40
B14: U$1.P$13, U$2.P$39
B15: U$1.P$18, U$2.P$38
C0: U$1.P$69, U$5.P$9
C1: U$1.P$68, U$5.P$44
C2: U$1.P$67, U$5.P$43
C3: U$1.P$66, U$5.P$42
C4: U$1.P$65, U$5.P$41
C5: U$1.P$64, U$5.P$40
C6: U$1.P$63, U$5.P$39
C7: U$1.P$62, U$5.P$38
C8: U$1.P$61, U$5.P$37
C9: U$1.P$60, U$5.P$2
C10: U$1.P$57, U$5.P$3
C11: U$1.P$56, U$5.P$4
C12: U$1.P$58, U$5.P$5
C13: U$1.P$55, U$5.P$6
C14: U$1.P$59, U$5.P$7
C15: U$1.P$54, U$5.P$8
D0: U$1.P$70, U$4.P$2
D1: U$1.P$39, U$4.P$37
D2: U$1.P$40, U$4.P$38
D3: U$1.P$41, U$4.P$39
D4: U$1.P$42, U$4.P$40
D5: U$1.P$43, U$4.P$41
D6: U$1.P$44, U$4.P$42
D7: U$1.P$45, U$4.P$43
D8: U$1.P$46, U$4.P$44
D9: U$1.P$47, U$4.P$9
D10: U$1.P$50, U$4.P$8
D11: U$1.P$51, U$4.P$7
D12: U$1.P$49, U$4.P$6
D13: U$1.P$52, U$4.P$5
D14: U$1.P$48, U$4.P$4
D15: U$1.P$53, U$4.P$3
GND: U$1.P$35, U$1.P$36, U$2.P$1, U$2.P$45, U$3.P$1, U$3.P$45, U$5.P$1, U$5.P$45
REF: U$1.P$1, U$1.P$2, U$1.P$38, U$2.P$10, U$2.P$36, U$3.P$10, U$3.P$36, U$4.P$10, U$4.P$36, U$5.P$10, U$5.P$36

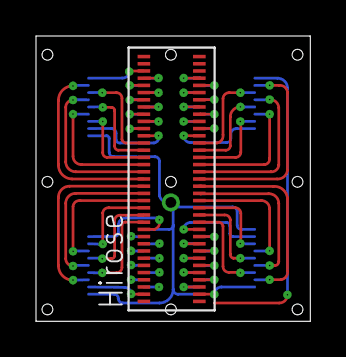
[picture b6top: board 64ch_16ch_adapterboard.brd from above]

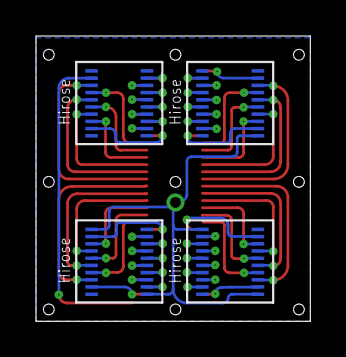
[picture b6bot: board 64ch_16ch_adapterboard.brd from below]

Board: 2 copper layers, 15.2 x 15.8 mm, 5 parts (4 on the bottom side), 66 nets.

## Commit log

2016-02-15 removing files to change organization scheme
2016-02-15 adding all current and old designs

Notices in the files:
Headstages/jmd_64ch_headstage/headstage.brd:
CC BY-SA JPN 2014
